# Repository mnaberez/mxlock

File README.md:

# MXLock

MXLock is a two-chip circuit that allows up to four mechanically locking keys (push-on, push-off) to be simulated using regular momentary key switches.

Many older computer keyboards have mechanically locking keys.  For example, the Commodore 128 has three locking keys: `SHIFT LOCK`, `CAPS LOCK`, and `40/80`.  The MXLock circuit can be included on the PCB of replacement keyboard projects, such as those using Cherry MX keys, so that the entire keyboard can be made from momentary key switches.

Features:

 - Simulates up to 4 locking keys using an [ATtiny214/414/814](https://web.archive.org/web/20231029180615if_/https://ww1.microchip.com/downloads/en/DeviceDoc/40001912A.pdf) and a [4066](https://web.archive.org/web/20231029180910if_/https://www.ti.com/lit/ds/symlink/cd4066b-mil.pdf)
 - Shows the on/off state of each key with LEDs
 - Remembers the lock states between power cycles (useful for mode keys like `40/80`)
 - Resets the computer by pulling `/RESET` low if the `LOCK0` key is held down
 - Puts the ATtiny to sleep between keypresses to save power

## Hardware

The [`hardware/`](./hardware/) directory in this repository contains the schematic and a PCB layout for the demonstration board pictured above.  It can be used to test the MXLock circuit.

The circuit is intended to be integrated directly onto the PCB of a keyboard.  Steve Gray's [C128SX keyboard](http://6502.org/users/sjgray/projects/mxkeyboards/) is an example of a keyboard using the circuit.

## Firmware

The firmware is written in AVR assembly language.  It can be assembled and flashed using open source software and inexpensive hardware.  See [`firmware/`](./firmware/) for the source code and instructions.

## Author

[Mike Naberezny](https://github.com/mnaberez)

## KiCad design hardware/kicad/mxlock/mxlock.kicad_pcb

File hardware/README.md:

# Hardware 

The MXLock circuit consists of two main components: an ATtiny214/414/814 microcontroller and a 4066 quad analog switch.  The momentary key switches are connected directly to the microcontroller.  The 4066 is connected to the computer's keyboard matrix.

Up to four locking keys can be simulated, `LOCK0` through `LOCK3`: 

 - `LOCK0` can also reset the computer if held down.  If the circuit on the demo board is used, the computer must have an active-low reset input (`/RESET`) like on the 6502.
 - `LOCK1` and `LOCK2` have no special characteristics.
 - `LOCK3` has the limitation that its LED that can't be turned off programmatically unless its 4066 contact is also turned off.  LOCK3 may also prevent the ATtiny from entering shutdown mode (see note below).   If fewer than four keys are required, choose the others instead.

The design files are in KiCad format.  A [PDF schematic](./schematic.pdf) and [Gerber files](./gerbers.zip) are also available.  The PCB is only for demonstration and testing purposes; the MXLock circuit is intended to be integrated onto a keyboard.

See [`firmware/`](../firmware) for how to program the microcontroller.

## Power Consumption

The ATtiny is put into full shutdown mode (CPU and internal oscillator stopped) between keypressess.  At 5.0 VDC, with no key being pressed down and the 4066 contacts all in the open state, the [Joulescope JS220](https://www.joulescope.com) measures the demo board as drawing about 140 nA / 0.140 μA.

The demo board consumes about 8.5 mA total when one of the contacts is closed and its LED is lit.  This power draw is dominated by the LED.  The board consumes about 8.5 * 4 = 34 mA when all four contacts are closed and their LEDs are lit.  Different LEDs and current limiting resistors can be used to reduce power.  The LEDs can also be omitted for the lowest possible current draw.

`LOCK3` should be avoided if power consumption is a concern as it may prevent the ATtiny from shutting down.  Pressing `LOCK3` a few times may put the ATtiny into a state where it draws about 1.5 mA between keypresses even though all contacts and LEDs are off.  In this state, pressing `LOCK3` a few more times may return the current draw to normal (~ 140 nA).  The input pin for `LOCK3` is shared with the UPDI interface.  Presumably, activity on this pin puts the chip's internal UPDI circuitry into a state where it draws more power.

Notes:

- If a UPDI programmer is connected, the power consumption of the demo board increases.  Disconnect UPDI before measuring current.

- If different LEDs or current limiting resistors are used, each LED must draw no more than 12 mA or else damage to the ATtiny may occur.

## EEPROM Life

The internal EEPROM of the ATtiny is used to restore the state of the keys after power is lost.  The EEPROM is updated whenever a key changes state.  The firmware uses a wear-leveling algorithm to spread writes across the EEPROM locations for maximum life.

Although the ATtiny214 is supported, it should be avoided if longevity is a concern:

The ATtiny414 and ATtiny814 are preferred because they have twice the EEPROM space (128 bytes) as the ATtiny214 (64 bytes).  The ATtiny214 should withstand 6.4 million key
changes, the ATtiny414 and ATtiny814 should withstand twice that at 12.8 million.  

## Parts List

The demo board uses the following components:

| Part | Qty | Reference Designators |
|------|-----|-------|
| [0.1uF 50V Capacitor](https://www.mouser.com/ProductDetail/594-K104M15X7RF53L2) | 2 | C1, C2 |
| [10uF 100V Capacitor](https://www.mouser.com/ProductDetail/661-E-101L100MF11D) | 1 | C3 |
| [T1-3/4 Green LED](https://www.mouser.com/ProductDetail/606-4304H5) | 4 | D1, D2, D3, D4 |
| [1x2 2.54mm Male Header](https://www.mouser.com/ProductDetail/649-1012937890201BLF) | 4 | J1, J2, J3, J4 |
| [10-pin 2x5 1.27mm Male Shrouded Header SMT](https://www.ebay.com/itm/171560426679) | 1 | J6 |
| [1x4 2.54mm Male Header](https://www.mouser.com/ProductDetail/649-1012937890401BLF) | 1 | J5 |
| [2N3904 Transistor](https://www.mouser.com/ProductDetail/512-2N3904BU) | 1 | Q1 |
| [330 ohm 1/4W Resistor](https://www.mouser.com/ProductDetail/603-MFR-25FTE52-330R) | 3 | R1, R2, R3, R4 |
| [1K 1/4W Resistor](https://www.mouser.com/ProductDetail/603-MFR-25FTF52-1K) | 1 | R5, R6 |
| [MX-Compatible Keyboard Switch](https://www.amazon.com/dp/B07K7J38SB) | 4 | SW1, SW2, SW3, SW4 |
| [ATtiny414-SSN](https://www.mouser.com/ProductDetail/579-ATTINY414-SSN) | 1 | U1 |
| [CD4066BM](https://www.mouser.com/ProductDetail/595-CD4066BM96) | 1 | U2 |

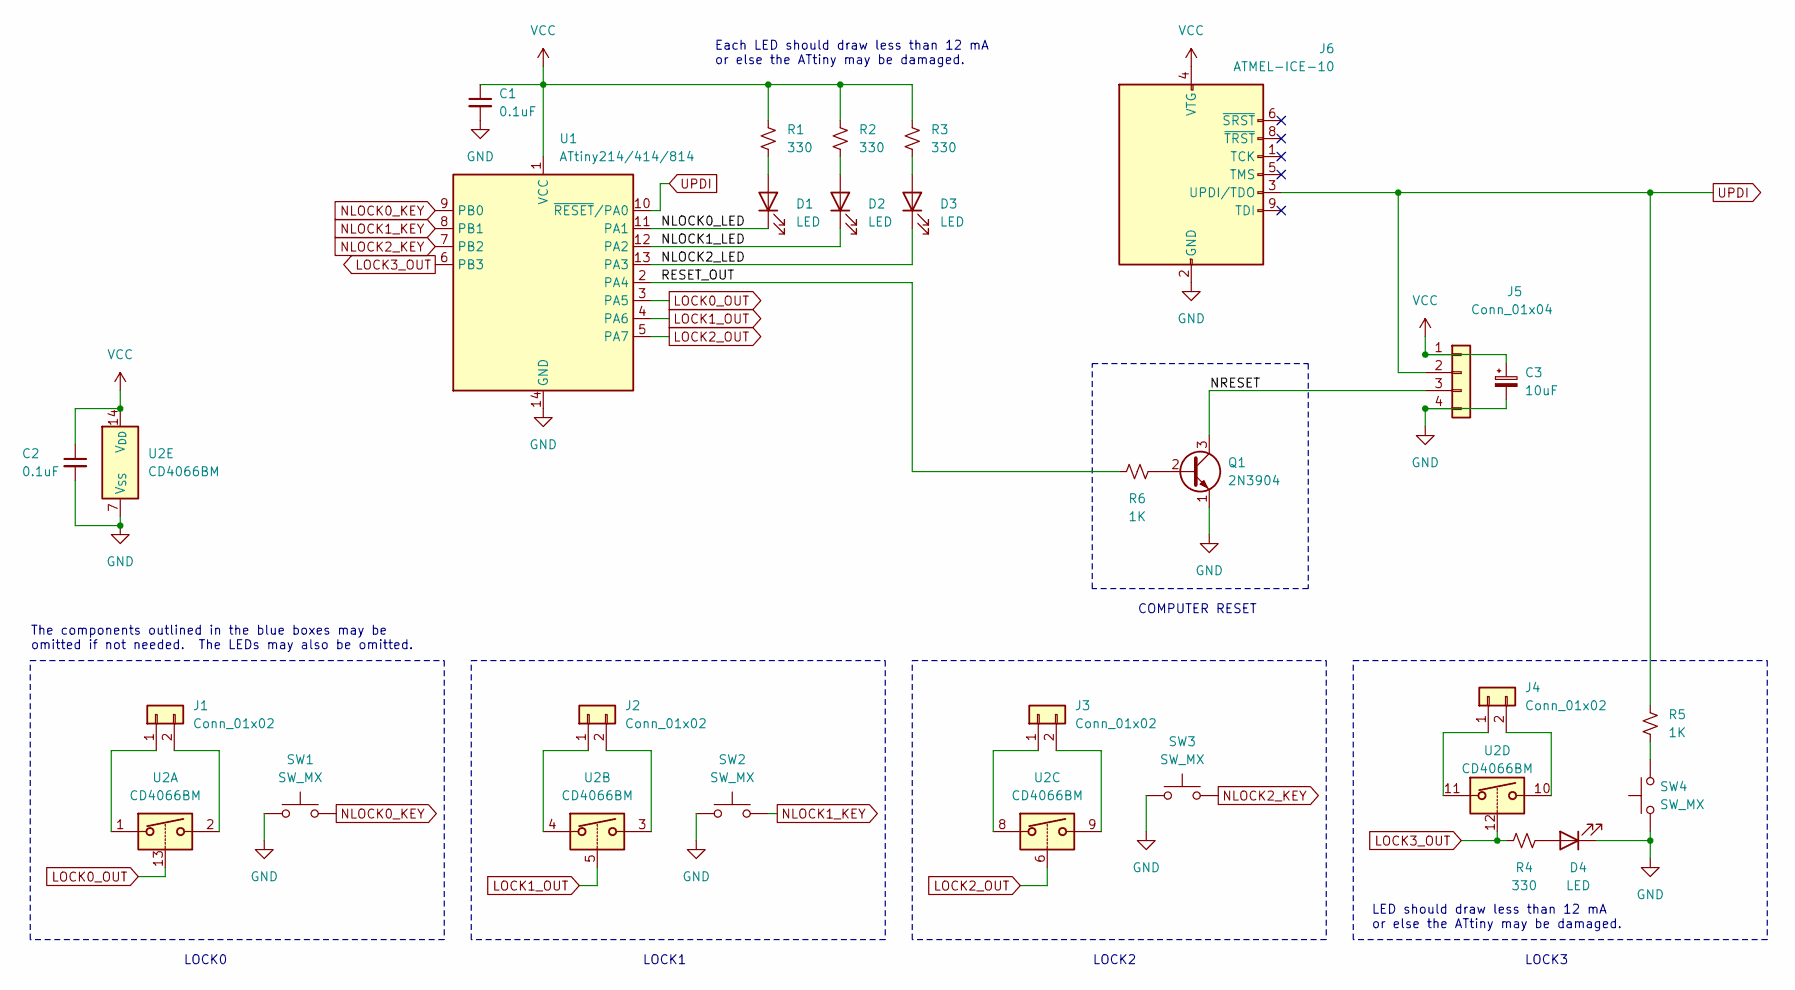
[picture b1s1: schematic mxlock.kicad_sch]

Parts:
C1, C2: 0.1uF; C_Disc_D5.0mm_W2.5mm_P5.00mm
C3: 10uF; CP_Radial_D6.3mm_P2.50mm
D1, D2, D3, D4: LED; LED_D5.0mm
J1, J2, J3, J4: Conn_01x02; PinHeader_1x02_P2.54mm_Vertical
J5: Conn_01x04; PinHeader_1x04_P2.54mm_Vertical
J6: ATMEL-ICE-10; PinHeader_2x05_P1.27mm_Shrouded_Vertical_SMD_Handsolder
Q1: 2N3904; TO-92_HandSolder
R1, R2, R3, R4: 330; R_Axial_DIN0204_L3.6mm_D1.6mm_P7.62mm_Horizontal
R5, R6: 1K; R_Axial_DIN0204_L3.6mm_D1.6mm_P7.62mm_Horizontal
SW1, SW2, SW3, SW4: SW_MX; SW_Cherry_MX_1.00u_PCB
U1: ATtiny214/414/814; SOIC-14_3.9x8.7mm_P1.27mm
U2: CD4066BM; SO-14_3.9x8.65mm_P1.27mm

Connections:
/NLOCK0_LED: D1.1 (K), U1.11 (PA1)
/NLOCK1_LED: D2.1 (K), U1.12 (PA2)
/NLOCK2_LED: D3.1 (K), U1.13 (PA3)
/NRESET: J5.3, Q1.3 (C)
/RESET_OUT: R6.1, U1.2 (PA4)
GND: C1.2, C2.2, C3.2, D4.1 (K), J5.4, J6.2 (GND), J6.10 (GND), Q1.1 (E), SW1.1, SW2.1, SW3.1, SW4.1, U1.14 (GND), U2.7 (V_{SS})
LOCK0_OUT: U1.3 (PA5), U2.13
LOCK1_OUT: U1.4 (PA6), U2.5
LOCK2_OUT: U1.5 (PA7), U2.6
LOCK3_OUT: R4.1, U1.6 (PB3), U2.12
NLOCK0_KEY: SW1.2, U1.9 (PB0)
NLOCK1_KEY: SW2.2, U1.8 (PB1)
NLOCK2_KEY: SW3.2, U1.7 (PB2)
unnamed: D1.2 (A), R1.2
unnamed: D2.2 (A), R2.2
unnamed: D3.2 (A), R3.2
unnamed: D4.2 (A), R4.2
unnamed: J1.1, U2.1
unnamed: J1.2, U2.2
unnamed: J2.1, U2.4
unnamed: J2.2, U2.3
unnamed: J3.1, U2.8
unnamed: J3.2, U2.9
unnamed: J4.1, U2.11
unnamed: J4.2, U2.10
unnamed: Q1.2 (B), R6.2
unnamed: R5.1, SW4.2
UPDI: J5.2, J6.3 (UPDI/TDO), R5.2, U1.10 (~RESET/PA0)
VCC: C1.1, C2.1, C3.1, J5.1, J6.4 (VTG), R1.1, R2.1, R3.1, U1.1 (VCC), U2.14 (V_{DD})

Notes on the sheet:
LOCK0
Each LED should draw less than 12 mA or else the ATtiny may be damaged.
LOCK3
LOCK1
COMPUTER RESET
The components outlined in the blue boxes may be omitted if not needed. The LEDs may also be omitted.
LED should draw less than 12 mA or else the ATtiny may be damaged.
LOCK2

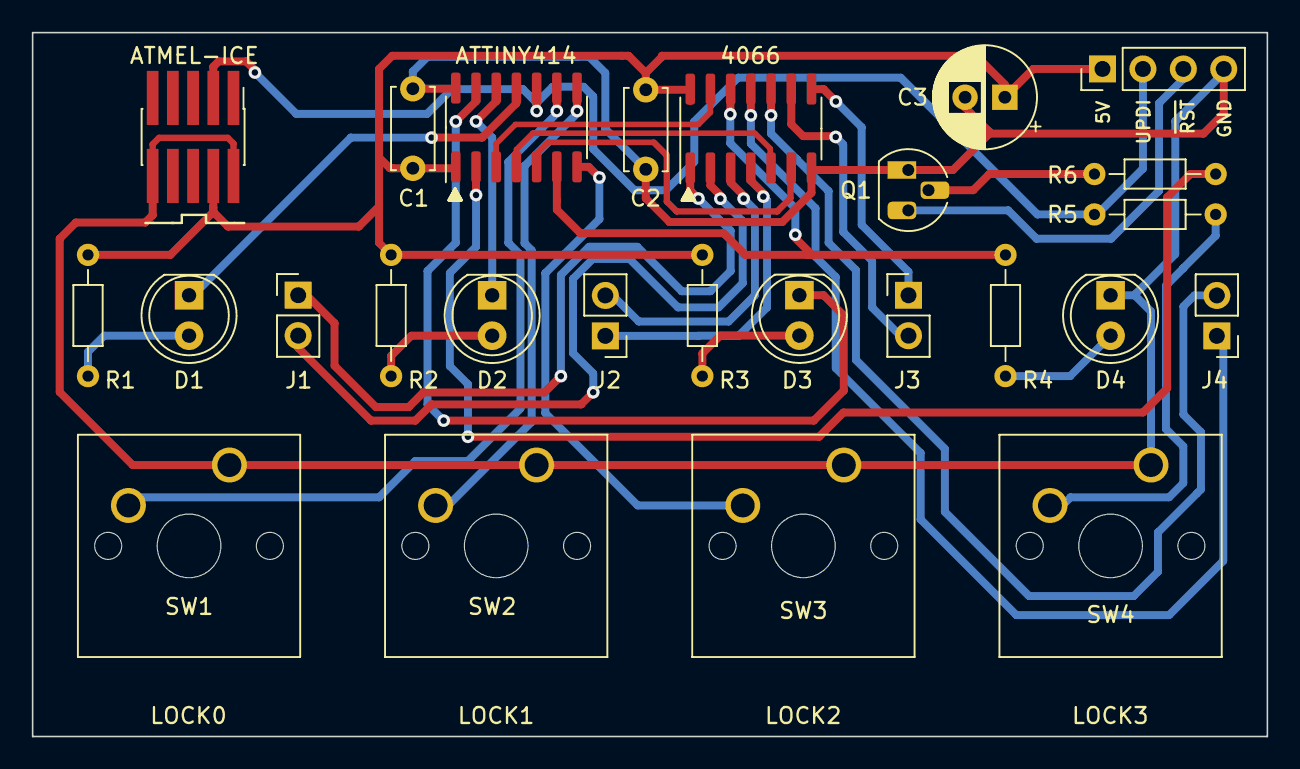
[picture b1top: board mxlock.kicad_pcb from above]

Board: 2 copper layers, 77.6 x 44.2 mm, 26 parts (0 on the bottom side), 29 nets.

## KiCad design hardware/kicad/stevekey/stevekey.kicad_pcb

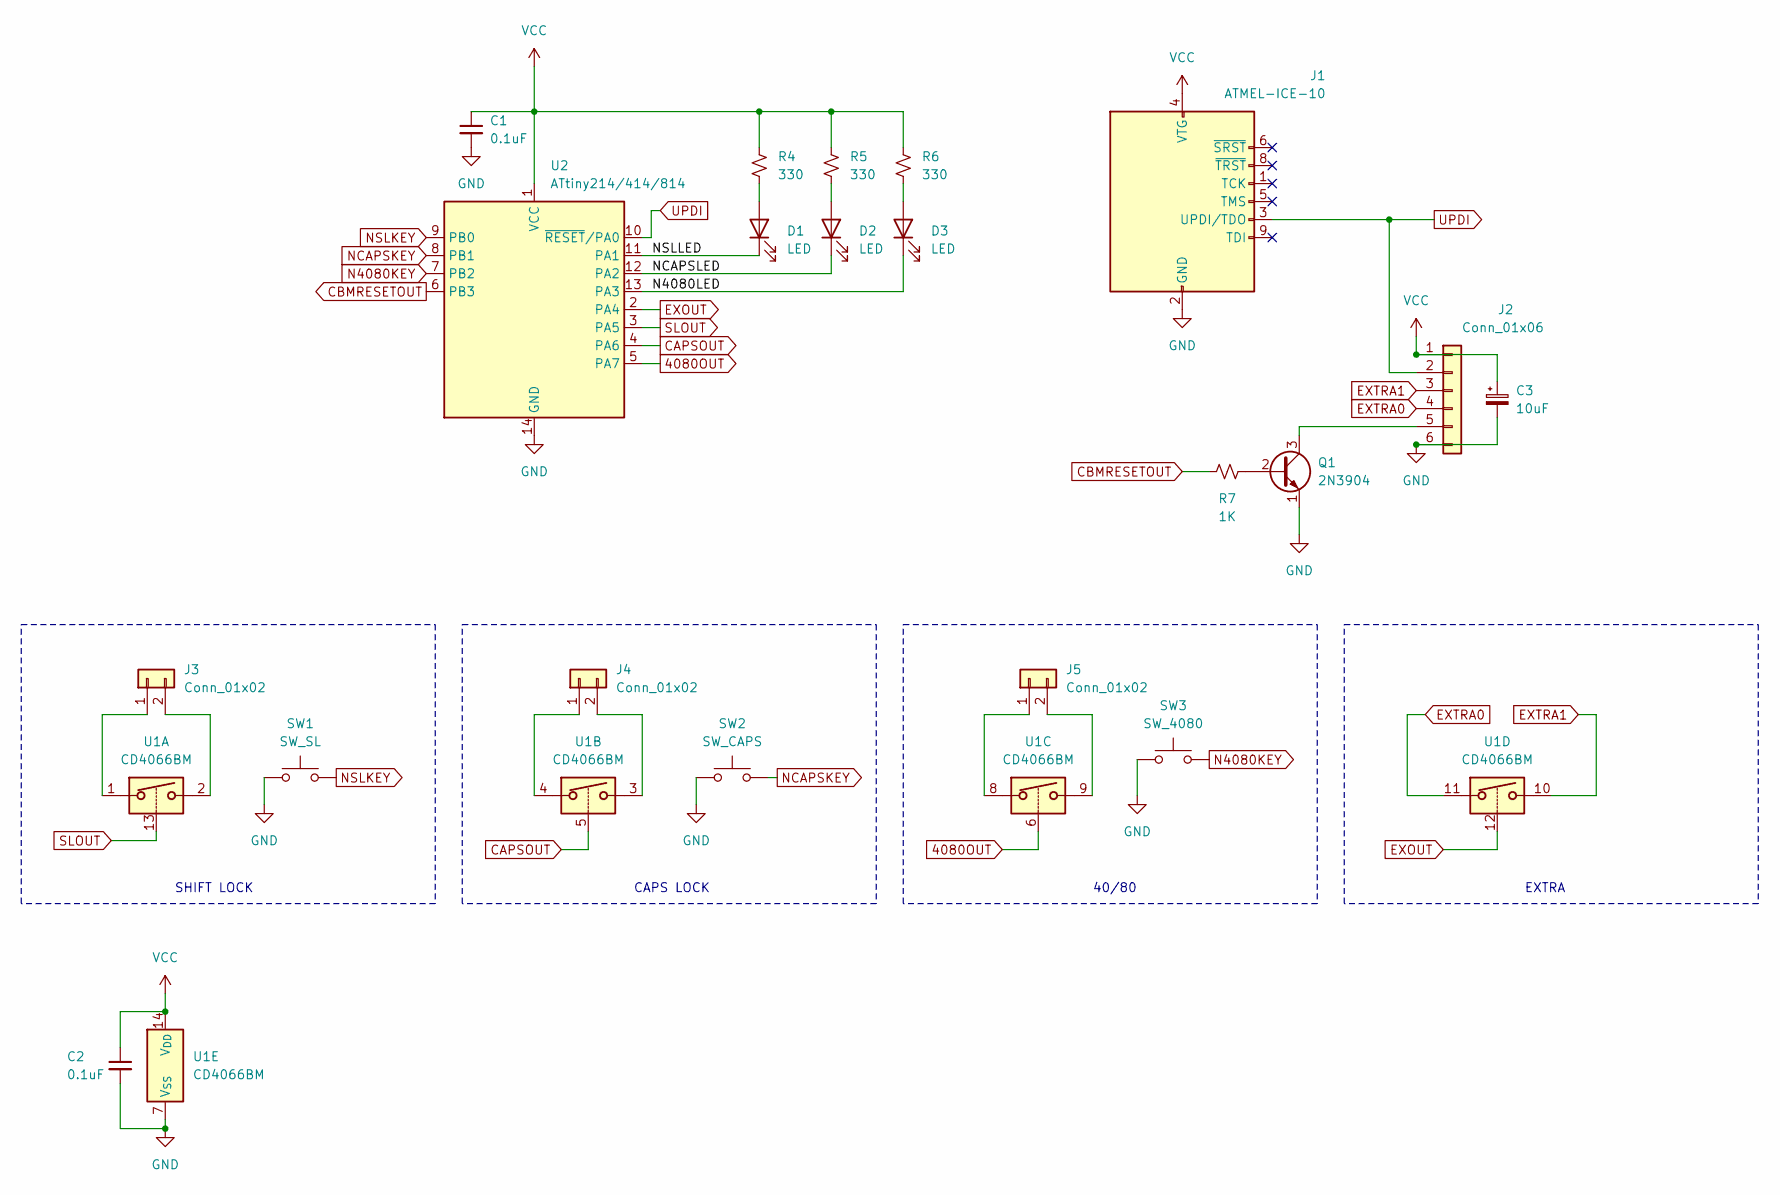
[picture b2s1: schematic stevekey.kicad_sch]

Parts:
C1, C2: 0.1uF; C_Disc_D5.0mm_W2.5mm_P5.00mm
C3: 10uF; CP_Radial_D6.3mm_P2.50mm
D1, D2, D3: LED; LED_D5.0mm
J1: ATMEL-ICE-10; PinHeader_2x05_P1.27mm_Shrouded_Vertical_SMD_Handsolder
J2: Conn_01x06; PinHeader_1x06_P2.54mm_Vertical
J3, J4, J5: Conn_01x02; PinHeader_1x02_P2.54mm_Vertical
Q1: 2N3904; TO-92_Inline
R4, R5, R6: 330; R_Axial_DIN0204_L3.6mm_D1.6mm_P7.62mm_Horizontal
R7: 1K; R_Axial_DIN0204_L3.6mm_D1.6mm_P7.62mm_Horizontal
SW1: SW_SL; SW_Cherry_MX_1.00u_PCB
SW2: SW_CAPS; SW_Cherry_MX_1.00u_PCB
SW3: SW_4080; SW_Cherry_MX_1.00u_PCB
U1: CD4066BM; SO-14_3.9x8.65mm_P1.27mm
U2: ATtiny214/414/814; SOIC-14_3.9x8.7mm_P1.27mm

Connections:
4080OUT: U1.6, U2.5 (PA7)
/N4080LED: D3.1 (K), U2.13 (PA3)
/NCAPSLED: D2.1 (K), U2.12 (PA2)
/NSLLED: D1.1 (K), U2.11 (PA1)
CAPSOUT: U1.5, U2.4 (PA6)
CBMRESETOUT: R7.1, U2.6 (PB3)
EXOUT: U1.12, U2.2 (PA4)
EXTRA0: J2.4, U1.11
EXTRA1: J2.3, U1.10
GND: C1.2, C2.2, C3.2, J1.2 (GND), J1.10 (GND), J2.6, Q1.1 (E), SW1.1, SW2.1, SW3.1, U1.7 (V_{SS}), U2.14 (GND)
N4080KEY: SW3.2, U2.7 (PB2)
NCAPSKEY: SW2.2, U2.8 (PB1)
NSLKEY: SW1.2, U2.9 (PB0)
unnamed: D1.2 (A), R4.2
unnamed: D2.2 (A), R5.2
unnamed: D3.2 (A), R6.2
unnamed: J2.5, Q1.3 (C)
unnamed: J3.1, U1.1
unnamed: J3.2, U1.2
unnamed: J4.1, U1.4
unnamed: J4.2, U1.3
unnamed: J5.1, U1.8
unnamed: J5.2, U1.9
unnamed: Q1.2 (B), R7.2
SLOUT: U1.13, U2.3 (PA5)
UPDI: J1.3 (UPDI/TDO), J2.2, U2.10 (~RESET/PA0)
VCC: C1.1, C2.1, C3.1, J1.4 (VTG), J2.1, R4.1, R5.1, R6.1, U1.14 (V_{DD}), U2.1 (VCC)

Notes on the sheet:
SHIFT LOCK
EXTRA
CAPS LOCK
40/80

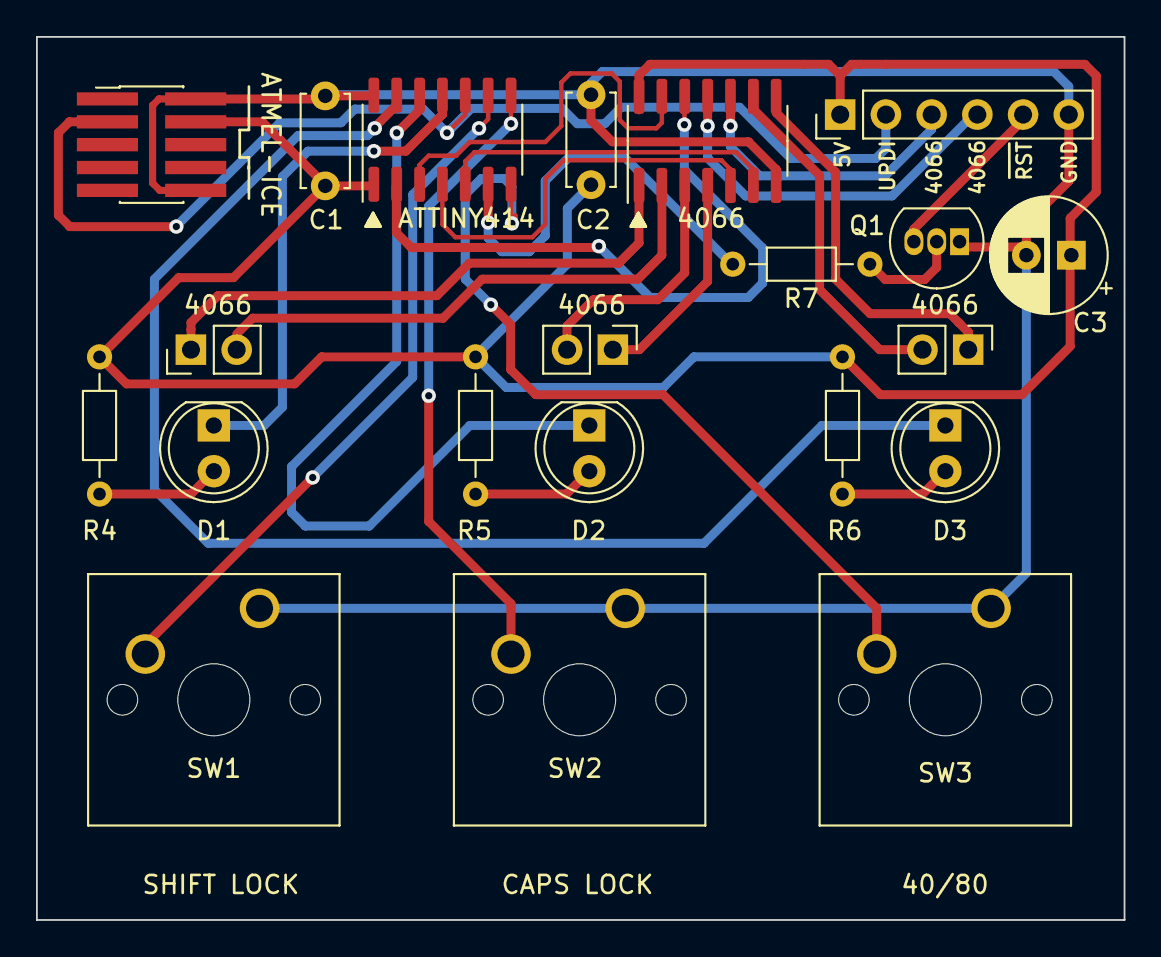
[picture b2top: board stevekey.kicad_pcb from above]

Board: 2 copper layers, 60.4 x 49.1 mm, 21 parts (0 on the bottom side), 27 nets.

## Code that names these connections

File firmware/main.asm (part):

;ATtiny214/ATtiny414/ATtiny814
;1  VCC
;2  PA4 out RESET_OUT (0=/RESET=open, 1=/RESET=low)
;3  PA5 out LOCK0_OUT to 4066 (0=off, 1=on)
;4  PA6 out LOCK1_OUT to 4066 (0=off, 1=on)
;5  PA7 out LOCK2_OUT to 4066 (0=off, 1=on)
;6  PB3 out LOCK3_OUT to 4066 and LED (0=off, 1=on)
;7  PB2 in /LOCK2_KEY (0=down, 1=up)
;8  PB1 in /LOCK1_KEY (0=down, 1=up)
;9  PB0 in /LOCK0_KEY (0=down, 1=up)
;10 UPDI/PA0 in /LOCK3_KEY (0=down, 1=up)
;11 PA1 out /LOCK0_LED (0=on, 1=off)
;12 PA2 out /LOCK1_LED (0=on, 1=off)
;13 PA3 out /LOCK2_LED (0=on, 1=off)
;14 GND

    ;Definitions file will be included first by the Makefile.
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    clr r16

    lds r17, PORTA_IN
    sbrs r17, 0             ;UPDI/PA0 clear
    ori r16, 1<<LOCK3       ;  sets LOCK3 bit

    lds r17, PORTB_IN
    sbrs r17, 2             ;PB2 clear
    ori r16, 1<<LOCK2       ;  sets LOCK2 bit
    sbrs r17, 1             ;PB1 clear
    ori r16, 1<<LOCK1       ;  sets LOCK1 bit
    sbrs r17, 0             ;PB0 clear
    ori r16, 1<<LOCK0       ;  sets LOCK0 bit

    pop r17
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    lds r17, PORTA_OUT
    andi r17, 0xff ^ (1<<7 | 1<<6 | 1<<5)
    sbrc r16, LOCK0    
    ori r17, 1<<5           ;LOCK0 bit set sets PA5
    sbrc r16, LOCK1     
    ori r17, 1<<6           ;LOCK1 bit set sets PA6
    sbrc r16, LOCK2         
    ori r17, 1<<7           ;LOCK2 bit set sets PA7
    sts PORTA_OUT, r17

    lds r17, PORTB_OUT
    andi r17, 0xff ^ (1<<3)
    sbrc r16, LOCK3
    ori r17, 1<<3           ;LOCK3 bit set sets PB3
    sts PORTB_OUT, r17

    pop r17
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
    lds r17, PORTA_OUT
    sbrc r17, 5                 
    ori r16, 1<<LOCK0       ;PA5 set sets LOCK0 bit
    sbrc r17, 6                 
    ori r16, 1<<LOCK1       ;PA6 set sets LOCK1 bit
    sbrc r17, 7                 
    ori r16, 1<<LOCK2       ;PA7 set sets LOCK2 bit

    lds r17, PORTB_OUT
    sbrc r17, 3
    ori r16, 1<<LOCK3       ;PB3 set sets LOCK3 bit

    pop r17
    ret
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    lds r17, PORTA_OUT
    andi r17, 0xff ^ (1<<3 | 1<<2 | 1<<1)    
    sbrs r16, LOCK0    
    ori r17, 1<<1           ;LOCK0 bit clear sets PA1
    sbrs r16, LOCK1     
    ori r17, 1<<2           ;LOCK1 bit clear sets PA2
    sbrs r16, LOCK2         
    ori r17, 1<<3           ;LOCK2 bit clear sets PA3
    sts PORTA_OUT, r17

    ;Note: The LED for LOCK3 is different.  It's ignored
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
    lds r17, PORTA_OUT
    sbrs r17, 1                 
    ori r16, 1<<LOCK0       ;PA1 clear sets LOCK0 bit
    sbrs r17, 2
    ori r16, 1<<LOCK1       ;PA2 clear sets LOCK1 bit
    sbrs r17, 3
    ori r16, 1<<LOCK2       ;PA3 clear sets LOCK2 bit

    ;Note: The LED for LOCK3 is different.  It's on whenever
    ;its 4066 contact is on, so the 4066 contact is tested here.

    lds r17, PORTB_OUT
    sbrc r17, 3
    ori r16, 1<<LOCK3       ;PB3 set sets LOCK3 bit

    pop r17
    ret
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;Pull the /RESET pin to GND, resetting the computer
;
gpio_reset_on:
    ldi r16, 1<<4           ;PA4
    sts PORTA_OUTSET, r16   ;set PA4=1 which pulls /RESET low
    ret

;Open the /RESET pin, allowing the computer to run
;
gpio_reset_off:
    ldi r16, 1<<4           ;PA4
    sts PORTA_OUTCLR, r16   ;set PA4=0 which makes /RESET open
    ret

;Set initial GPIO directions and states
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; - Key pins as inputs
; - LED pins as outputs; LEDs not lit
; - 4066 pins as outputs; contacts open
; - RESET_OUT pin as output; /RESET=open
;
gpio_init:
    ;Key Inputs
    ldi r16, 1<<2 | 1<<1 | 1<<0     ;PB2, PB1, PB0
    sts PORTB_DIRCLR, r16           ;Set pins as input

    ;Enable pull-ups and pin-change interrupts
    ldi r16, PORT_PULLUPEN_bm | PORT_ISC_BOTHEDGES_gc
    sts PORTB_PIN2CTRL, r16         ; on PB2
    sts PORTB_PIN1CTRL, r16         ; on PB1
    sts PORTB_PIN0CTRL, r16         ; on PB0

    ;UPDI/PA0 Key Input
    ldi r16, 1<<0                   ;UPDI/PA0
    sts PORTA_DIRCLR, r16           ;Set UPDI pin also as a GPIO input
    ldi r16, PORT_ISC_BOTHEDGES_gc
    sts PORTA_PIN0CTRL, r16         ;Enable pin change interrupt on PA0

    ;Note: The UPDI/PA0 pin is configured for UPDI in the fuses.  In UPDI
    ;mode, the pin can still be used as an input.  The MCU can still be
    ;programmed with UPDI as long as the key is not pressed down.  No pull-up
    ;is configured because UPDI mode has its own special pull-up.

    ;4066 Outputs
    ldi r16, 1<<7 | 1<<6 | 1<<5     ;PA7, PA6, PA5
    sts PORTA_OUTCLR, r16           ;Set 4066s initially off (0=off)
    sts PORTA_DIRSET, r16           ;Set pins as outputs
    ldi r16, 1<<3                   ;PB3
    sts PORTB_OUTCLR, r16           ;Set 4066s initially off (0=off)
    sts PORTB_DIRSET, r16           ;Set pins as outputs

    ;LED Outputs
    ldi r16, 1<<3 | 1<<2 | 1<<1     ;PA3, PA2, PA1
    sts PORTA_OUTSET, r16           ;Sets LEDs initially off (1=off)
    sts PORTA_DIRSET, r16           ;Set pins as outputs

    ;RESET_OUT Output
    ldi r16, 1<<4                   ;PA4
    sts PORTA_OUTCLR, r16           ;Set RESET_OUT initially off (0=off)
    sts PORTA_DIRSET, r16           ;Set PA4 as output
    ret

;SLEEP ======================================================================
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
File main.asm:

;ATtiny214
;1  VCC
;2  PA4 out EXTRAOUT to 4066 (0=off, 1=on)
;3  PA5 out SLOUT 
;4  PA6 out CAPSOUT 
;5  PA7 out 4080OUT 
;6  PB3 NC
;7  PB2 in 4080KEY (0=down, 1=up)
;8  PB1 in CAPSKEY 
;9  PB0 in SLKEY 
;10 UPDI
;11 PA1 out SLLED (0=on, 1=off)
;12 PA2 out CAPSLED
;13 PA3 out 4080LED 
;14 GND

    ;Definitions file "tn214def.asm"
    ;will be included first by the Makefile.

    .area code (abs)
    .list (me)

    .org PROGMEM_START/2  ;/2 because PROGMEM_START constant is byte-addressed
                          ;but ASAVR treats program space as word-addressed.
    rjmp reset

    ;All interrupt vectors jump to fatal error (interrupts are not used)
    .rept INT_VECTORS_SIZE - 1
    rjmp fatal
    .endm

    ;Code starts at first location after vectors
    .assume . - ((PROGMEM_START/2) + INT_VECTORS_SIZE)

reset:
    ;Clear RAM
    ldi ZL, <INTERNAL_SRAM_START
    ldi ZH, >INTERNAL_SRAM_START
    clr r16
1$: st Z, r16                 ;Store 0 at Z
    ld r16, Z+                ;Read it back, increment Z
    tst r16                   ;Did it read back as 0?
    breq 2$                   ;Yes: continue clearing
    rjmp fatal                ;No: hardware failure, jump to fatal
2$: cpi ZL, <(INTERNAL_SRAM_END+1)
    brne 1$
    cpi ZH, >(INTERNAL_SRAM_END+1)
    brne 1$

    ;Initialize stack pointer
    ldi r16, <INTERNAL_SRAM_END
    out CPU_SPL, r16
    ldi r16, >INTERNAL_SRAM_END
    out CPU_SPH, r16

    rcall wdog_init
    rcall gpio_init

main_loop:
    wdr                       ;Keep watchdog happy
    rjmp main_loop

;Set up GPIO directions (UART pin directions are set in uart_init)
gpio_init:
    ldi r16, 1<<2 | 1<<1    ;PA2, PA1 = input
    sts PORTA_DIRCLR, r16
    ret

;Ensure the watchdog was started by the fuses and reset the timer.
;The WDR instruction must be executed at least once every 4 seconds
;or the watchdog will reset the system.
wdog_init:
    ;Ensure watchdog period has been configured
    lds r16, WDT_CTRLA
    andi r16, WDT_PERIOD_gm
    cpi r16, WDT_PERIOD_4KCLK_gc      ;Watchdog period set by the fuses?
    breq 1$                           ;Yes: continue
    rjmp fatal                        ;No: bad fuses, jump to fatal

    ;Ensure watchdog is locked so it can't be stopped
1$: lds r16, WDT_STATUS
    sbrs r16, WDT_LOCK_bp             ;Skip fatal if locked
    rjmp fatal

    wdr                               ;Reset watchdog timer
    ret

;Wait 1ms.  Destroy R16,R17
delay_1ms:
    ldi r16, 6
1$: ldi r17, 0xc5
2$: dec r17
    brne 2$
    dec r16
    brne 1$
    ret

;End of code

    ;Fill all unused program words with a nop sled that ends with
    ;a software reset in case the program counter somehow gets here.
    .nval filler_start,.
    .rept ((PROGMEM_END/2) - filler_start - fatal_size)
    nop
    .endm

;Fatal error causes software reset
fatal:
    cli                       ;Disable interrupts
    ldi r16, CPU_CCP_IOREG_gc
    ldi r17, RSTCTRL_SWRE_bm
    out CPU_CCP, r16          ;Unlock Protected I/O Registers
    sts RSTCTRL_SWRR, r17     ;Software Reset

fatal_size = . - fatal

;Last program word (last 2 bytes) will be the CRC16 added by the Makefile
crc16:
    .assume . - (PROGMEM_END/2)

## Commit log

2023-08-26 Ignore build outputs
2023-08-26 Add project skeleton
2023-08-26 Add GitHub Actions workflow
2023-08-26 Build for ATtiny214
2023-08-26 Remove ROM test since it's done automatically on reset
2023-10-01 Move firmware to firmware/
2023-10-02 Start schematic
2023-10-08 Start board layout
2023-10-11 Initial routing is complete
2023-10-11 Add transistor to pull /RES down
2023-10-11 Bring the extra 4066 pins out to the header
2023-10-11 Remove old KiCad backup files
2023-10-11 Fix values of C1 and C2
2023-10-11 Add capacitor on input power
2023-10-11 Add directory for Gerber outputs
2023-10-11 Minor layout tweaks
2023-10-11 Write Gerbers to gerbers/
2023-10-11 Add PDF schematic and Gerber files
2023-10-13 Build using ASxxxx 5.50
2023-10-27 Pushing button sets LED and 4066 contact
2023-10-27 Clean up the GPIO routines a bit
2023-10-27 Add routines to control /CBMRESET
2023-10-27 Add corresponding read routines for all ports
2023-10-27 Add 20ms debounce
2023-10-28 Add license (BSD 3-clause)
2023-10-28 Add README
2023-10-28 Add photo of board
2023-10-29 Fix typo in build step name
2023-10-29 Link to datasheets
2023-10-29 Add parts list
2023-10-30 Fix detection when another key is held down
2023-10-30 Hold down Shift Lock to reset
2023-10-31 Save a few instructions when checking keys
2023-10-31 Separate reset into its own task
2023-11-01 Add routine to wait N milliseconds
2023-11-01 Initialize EEPROM during programming
2023-11-01 Restore 4066 contacts from EEPROM
2023-11-01 Fix double reset when Shift Lock is held down
2023-11-01 Run with 20 MHz internal oscillator
2023-11-01 Remember latch states in EEPROM
2023-11-01 Check all keys in a single task
2023-11-01 Add constant for Shift Lock hold time
2023-11-04 Turn off LEDs during EEPROM write
2023-11-04 Add definitions file for ATtiny414
2023-11-04 Add definitions file for ATtiny814
2023-11-04 Add ATtiny414 and ATtiny814 build targets
2023-11-04 Use a matrix to build all versions
2023-11-04 Implement EEPROM wear leveling
2023-11-05 Add note that ATtiny414 and ATtiny814 are supported
2023-11-05 Use 330 ohm resistor for LEDs
2023-11-05 Use internal pull-ups for keys
2023-11-05 Use "mxlock" for project files
2023-11-05 Use UPDI/PA0 as a fourth key input
2023-11-05 Add fourth key to the schematic
2023-11-05 Update parts list for the fourth key
2023-11-06 Fix typo in readme
2023-11-07 Add fourth key to the PCB layout
2023-11-07 Use consistent reference designators
2023-11-08 Rename keys to LOCK0-3
2023-11-08 Add PDF schematic and gerbers for Rev 2
2023-11-09 Fix typo in signal name
2023-11-12 Update README for fourth key support
2023-11-12 Outline reset circuit on schematic
2023-11-12 Add hardware info
2023-11-18 Build for ATtiny414 by default
2023-11-18 Fix typos
2023-11-19 Update before installing srecord
2023-11-19 Fix indentation
2023-11-19 Update GPIO routines for Rev 2
2023-11-19 Add photo of Rev 2
2023-11-19 Fix typo
2023-11-20 Clarify intended use
2023-11-20 Add links to other circuits
2023-11-21 Add firmware build instructions
2023-11-21 Drop down to 1 MHz to save a little power
2024-05-26 Ignore KiCad autosave files
2024-05-27 Upgrade to KiCad 8
2024-05-27 Update copyright year to 2024
2024-05-27 Remove unnecessary RAM clear to reduce startup time
2024-05-28 Remove unnecessary CRCSCAN check to reduce startup time
2024-05-28 Upgrade deprecated GitHub Actions steps
2024-09-19 Sleep between keypresses to save power
2025-09-22 Update to KiCad 9 format
2025-11-16 Fix hang at power-on caused by ccdb1fbb6e46af6dde97c36fcbb627271af4deb3
2025-11-17 Update copyright year to 2025
2025-11-17 Read keys in a task for better organization
2025-11-18 Add notes on power consumption and EEPROM life
2026-05-29 Upgrade outdated GitHub actions

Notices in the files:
hardware/kicad/mxlock/mxlock.kicad_pcb:
MXLOCK DEMO BOARD REV. 2 © 2023 MIKE NABEREZNY
hardware/kicad/stevekey/stevekey.kicad_pcb:
STEVEKEY MCU DEV BOARD REV. 2 © 2023 MIKE NABEREZNY
